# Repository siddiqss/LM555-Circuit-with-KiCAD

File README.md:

# LM555-Circuit-with-KiCAD
##### This a simple Schematic and PCB Design of a circuit with LM555 (Timer) made with KiCAD.
---
## Requirements
KiCAD - [Download here](http://kicad-pcb.org/download/).

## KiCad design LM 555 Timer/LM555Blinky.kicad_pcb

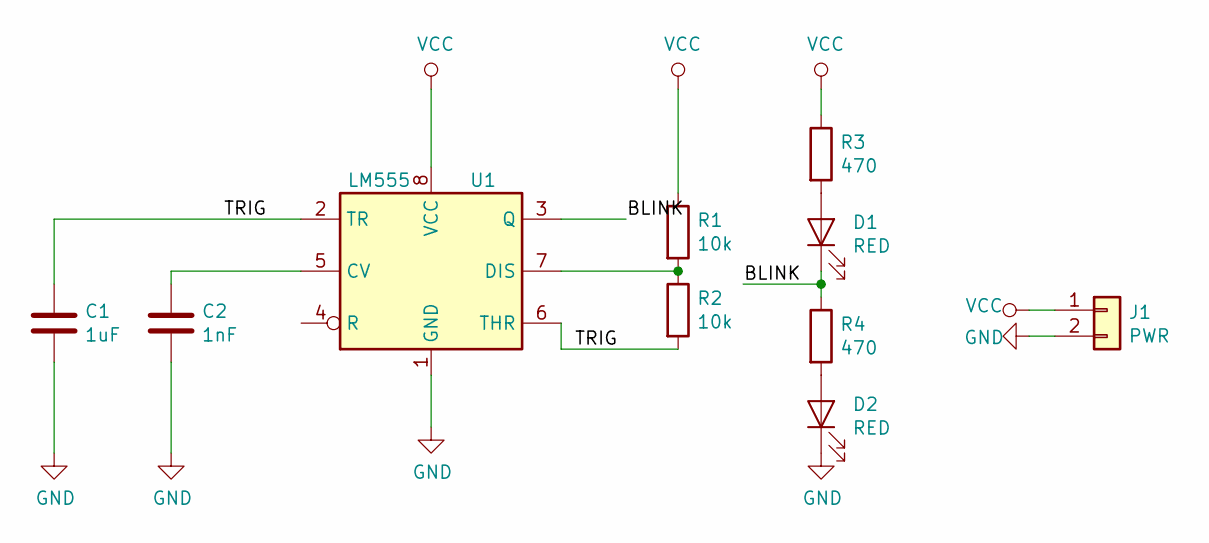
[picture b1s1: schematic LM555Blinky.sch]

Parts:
C1: 1uF; CP_Radial_D10.0mm_P3.80mm
C2: 1nF; C_Axial_L3.8mm_D2.6mm_P7.50mm_Horizontal
D1, D2: RED; LED_D5.0mm
J1: PWR; PinHeader_1x02_P2.54mm_Vertical
R1, R2: 10k; R_Axial_DIN0207_L6.3mm_D2.5mm_P10.16mm_Horizontal
R3, R4: 470; R_Axial_DIN0207_L6.3mm_D2.5mm_P10.16mm_Horizontal
U1: LM555; DIP-8_W7.62mm

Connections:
/BLINK: D1.1 (K), R4.1, U1.3 (Q)
/TRIG: C1.1, R2.2, U1.2 (TR), U1.6 (THR)
GND: C1.2, C2.2, D2.1 (K), J1.2, U1.1 (GND)
unnamed: C2.1, U1.5 (CV)
unnamed: D1.2 (A), R3.2
unnamed: D2.2 (A), R4.2
unnamed: R1.2, R2.1, U1.7 (DIS)
VCC: J1.1, R1.1, R3.1, U1.8 (VCC)

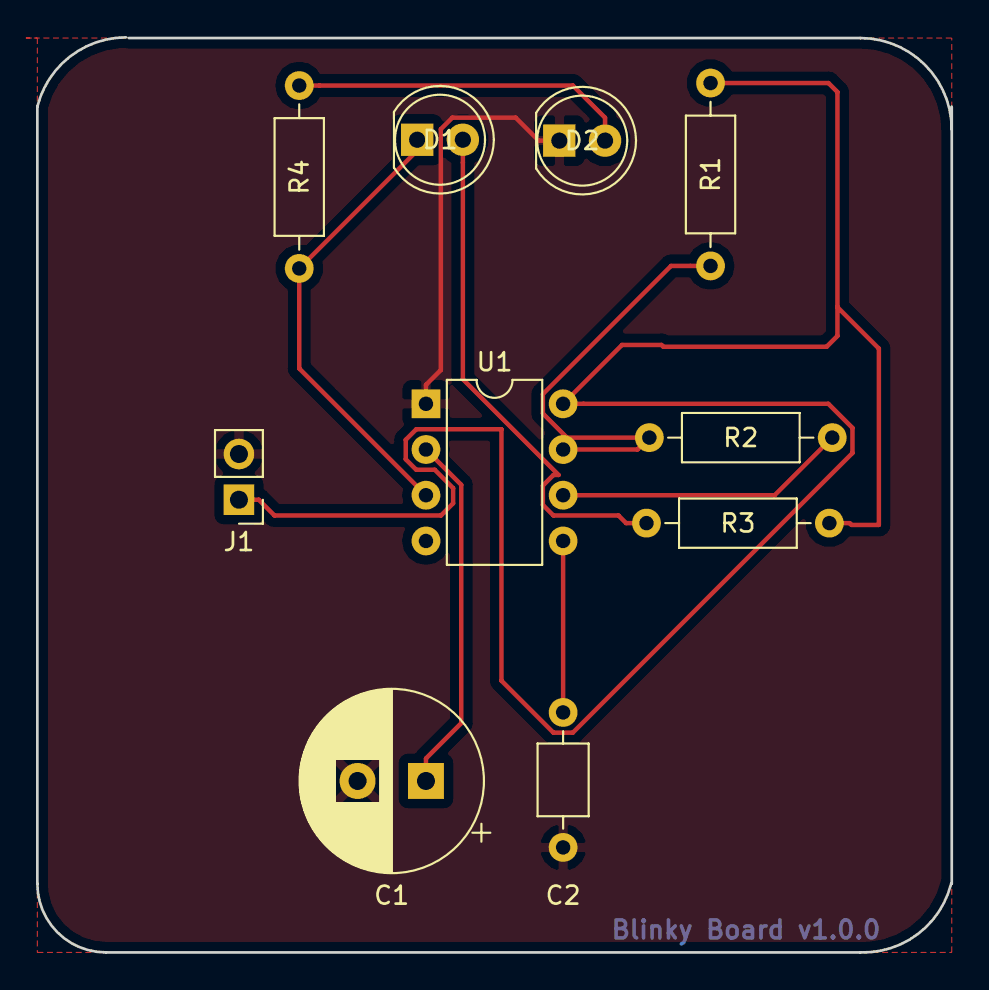
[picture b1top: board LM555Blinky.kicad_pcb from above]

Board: 2 copper layers, 50.8 x 50.8 mm, 10 parts (0 on the bottom side), 8 nets.

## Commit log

2019-03-28 All Files Uploaded
2019-03-28 New Folder Created
2019-03-28 Files Uploaded!
2019-03-28 Rename out.txt to out
2019-03-28 Output Files Uploaded!
